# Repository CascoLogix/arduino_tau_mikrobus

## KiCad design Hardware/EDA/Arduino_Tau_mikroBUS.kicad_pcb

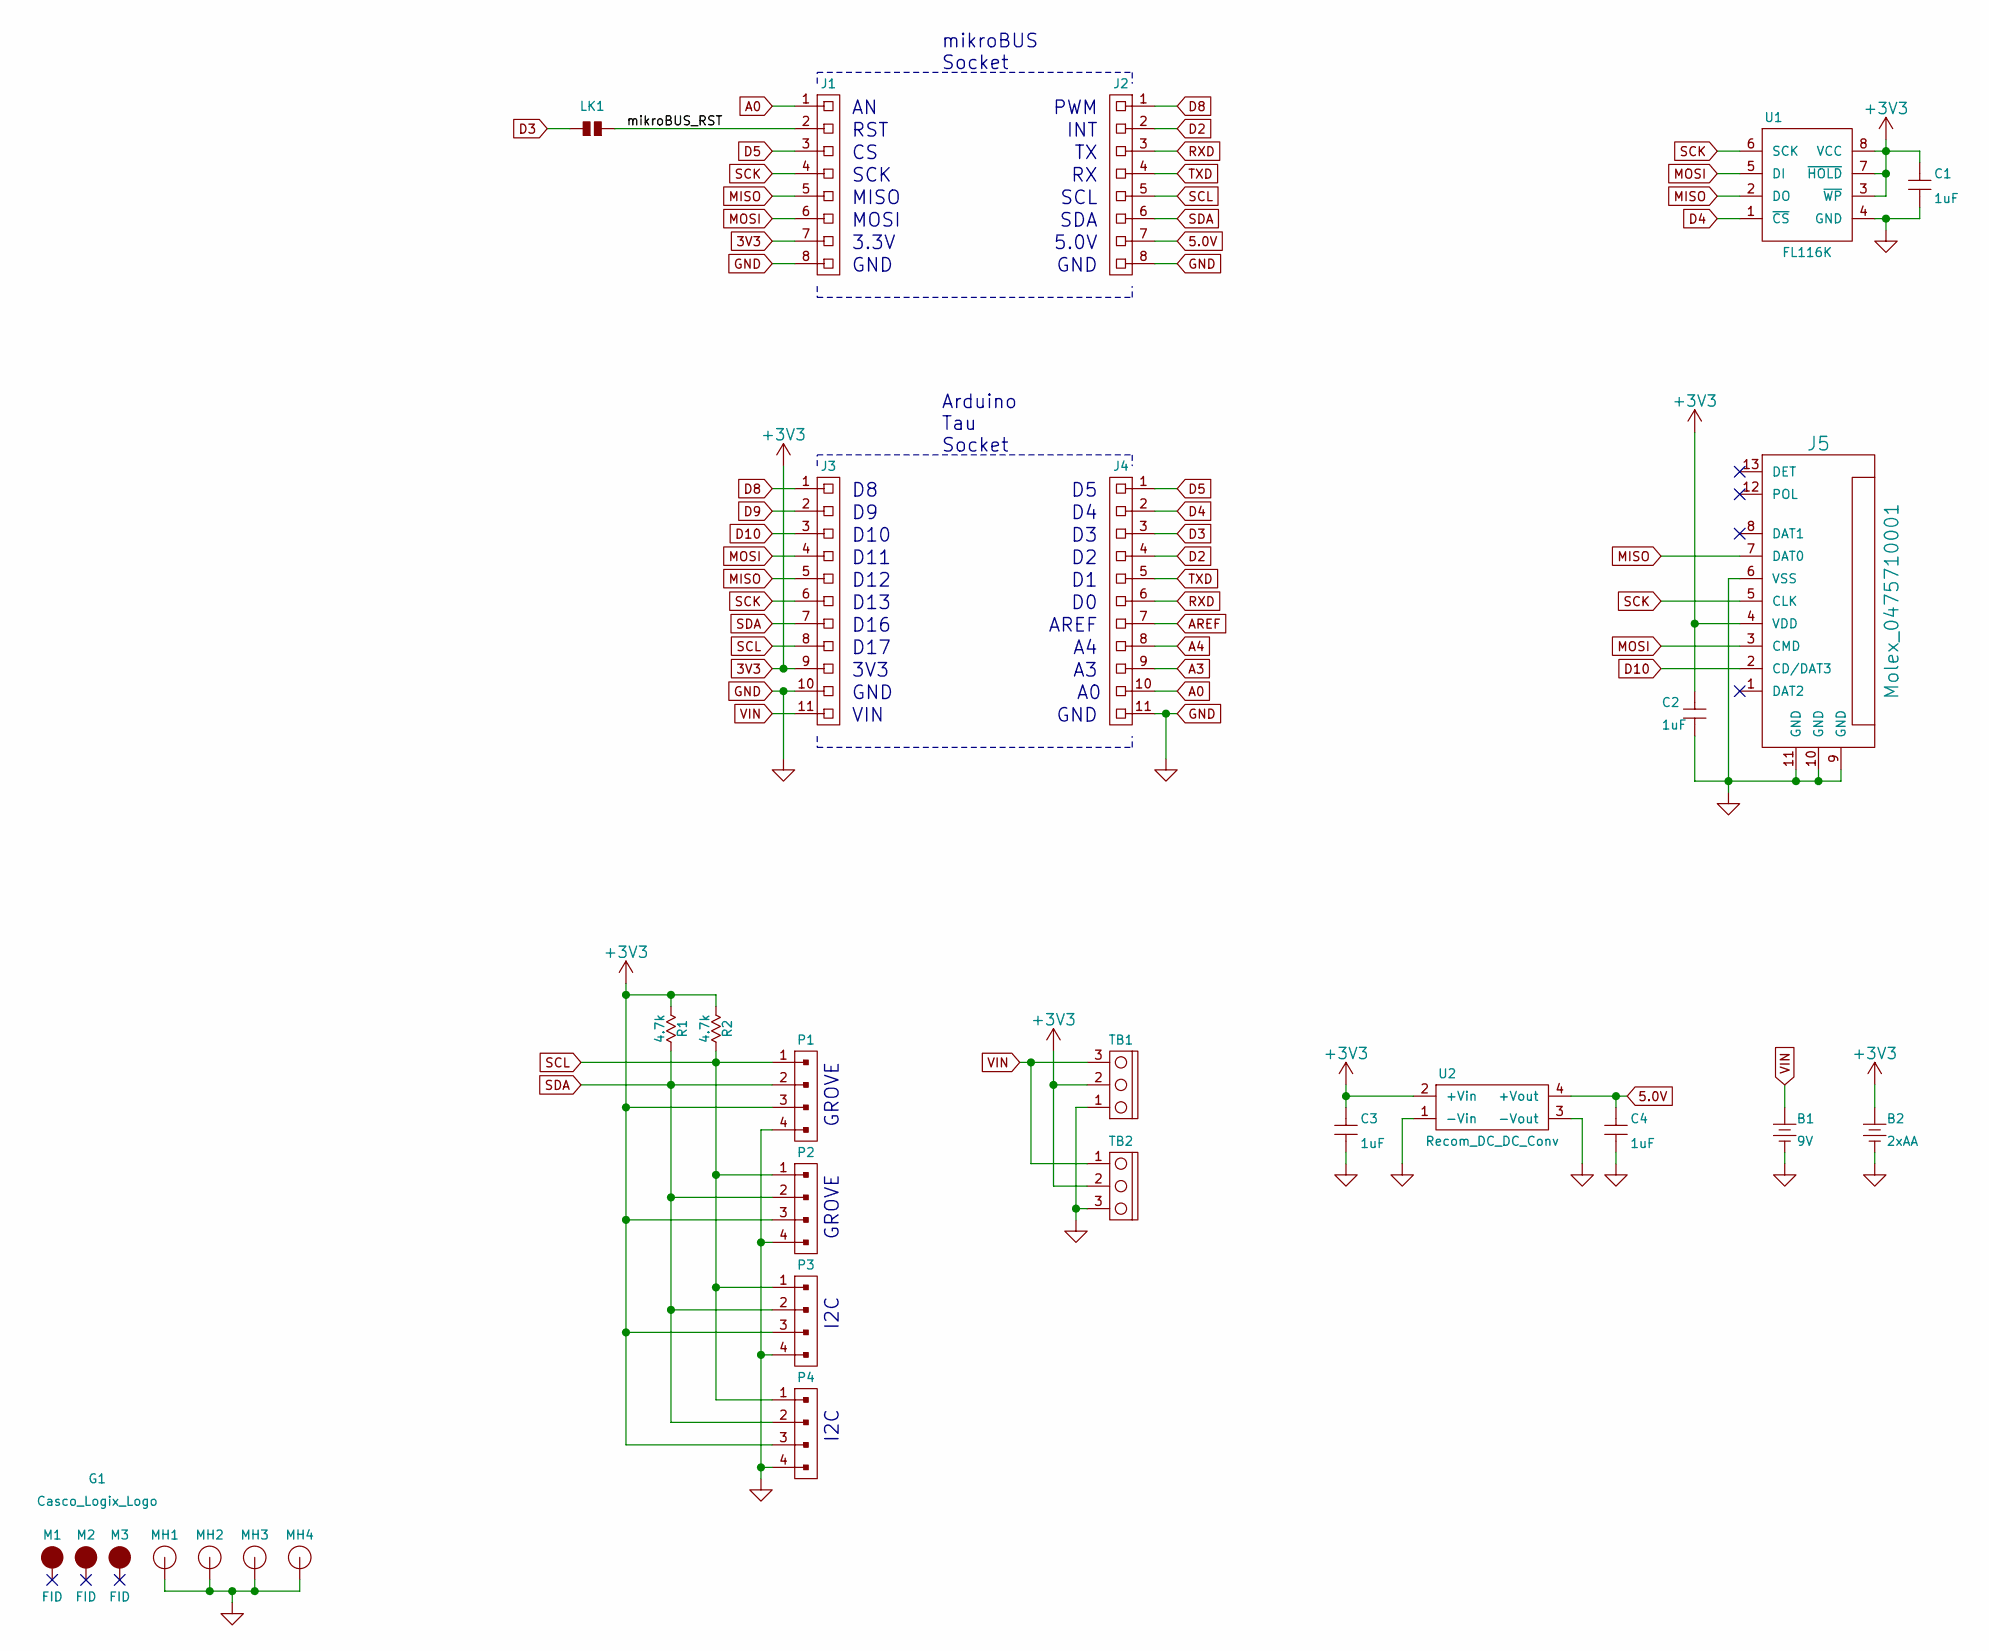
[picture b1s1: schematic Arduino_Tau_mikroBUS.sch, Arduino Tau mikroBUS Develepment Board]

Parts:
B1: 9V; BC9VPC
B2: 2xAA; Keystone_2462_2AA
C1, C2, C3, C4: 1uF; 0603
G1: Casco_Logix_Logo; Casco_Logix_Logo_7x7MM
J1, J2: HEADER_F_2.54MM_1R8P_ST_AU_PTH
J3, J4: HEADER_F_2.54MM_1R11P_ST_AU_PTH
J5: Molex_0475710001
LK1: SOLDER_LINK_NO
M1, M2, M3: FID; FIDUCIAL
MH1, MH2, MH3, MH4: MTG_HOLE; MH_#6
P1, P2, P3, P4: HEADER_M_2.54MM_1R4P_ST_AU_PTH
R1, R2: 4.7k; R0603
TB1, TB2: OSTVN_1x3; TB_100MIL_1R3P_PTH
U1: FL116K; SO-8
U2: Recom_DC_DC_Conv; Recom_ROE-3.305S

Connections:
3V3: B2.1 (+), C1.1, C2.1, C3.1, J1.7, J3.9, J5.4 (VDD), P1.3, P2.3, P3.3, P4.3, R1.1, R2.1, TB1.2, TB2.2, U1.3 (~WP), U1.7 (~HOLD), U1.8 (VCC), U2.2 (+Vin)
5.0V: C4.1, J2.7, U2.4 (+Vout)
/mikroBUS_RST: J1.2, LK1.2
A0: J1.1, J4.10
A3: J4.9
A4: J4.8
AREF: J4.7
D2: J2.2, J4.4
D3: J4.3, LK1.1
D4: J4.2, U1.1 (~CS)
D5: J1.3, J4.1
D8: J2.1, J3.1
D9: J3.2
D10: J3.3, J5.2 (CD/DAT3)
GND: B1.2 (-), B2.2 (-), C1.2, C2.2, C3.2, C4.2, J1.8, J2.8, J3.10, J4.11, J5.6 (VSS), J5.9 (GND), J5.10 (GND), J5.11 (GND), MH1.~, MH2.~, MH3.~, MH4.~, P1.4, P2.4, P3.4, P4.4, TB1.1, TB2.3, U1.4 (GND), U2.1 (-Vin), U2.3 (-Vout)
MISO: J1.5, J3.5, J5.7 (DAT0), U1.2 (DO)
MOSI: J1.6, J3.4, J5.3 (CMD), U1.5 (DI)
RXD: J2.3, J4.6
SCK: J1.4, J3.6, J5.5 (CLK), U1.6 (SCK)
SCL: J2.5, J3.8, P1.1, P2.1, P3.1, P4.1, R2.2
SDA: J2.6, J3.7, P1.2, P2.2, P3.2, P4.2, R1.2
TXD: J2.4, J4.5
VIN: B1.1 (+), J3.11, TB1.3, TB2.1

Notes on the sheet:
mikroBUS Socket
Arduino Tau Socket
RST
SCK
MISO
MOSI
3.3V
GND
PWM
INT
SCL
SDA
5.0V
D10
3V3
VIN
AREF
GROVE
I2C
D11
D12
D13
D16
D17

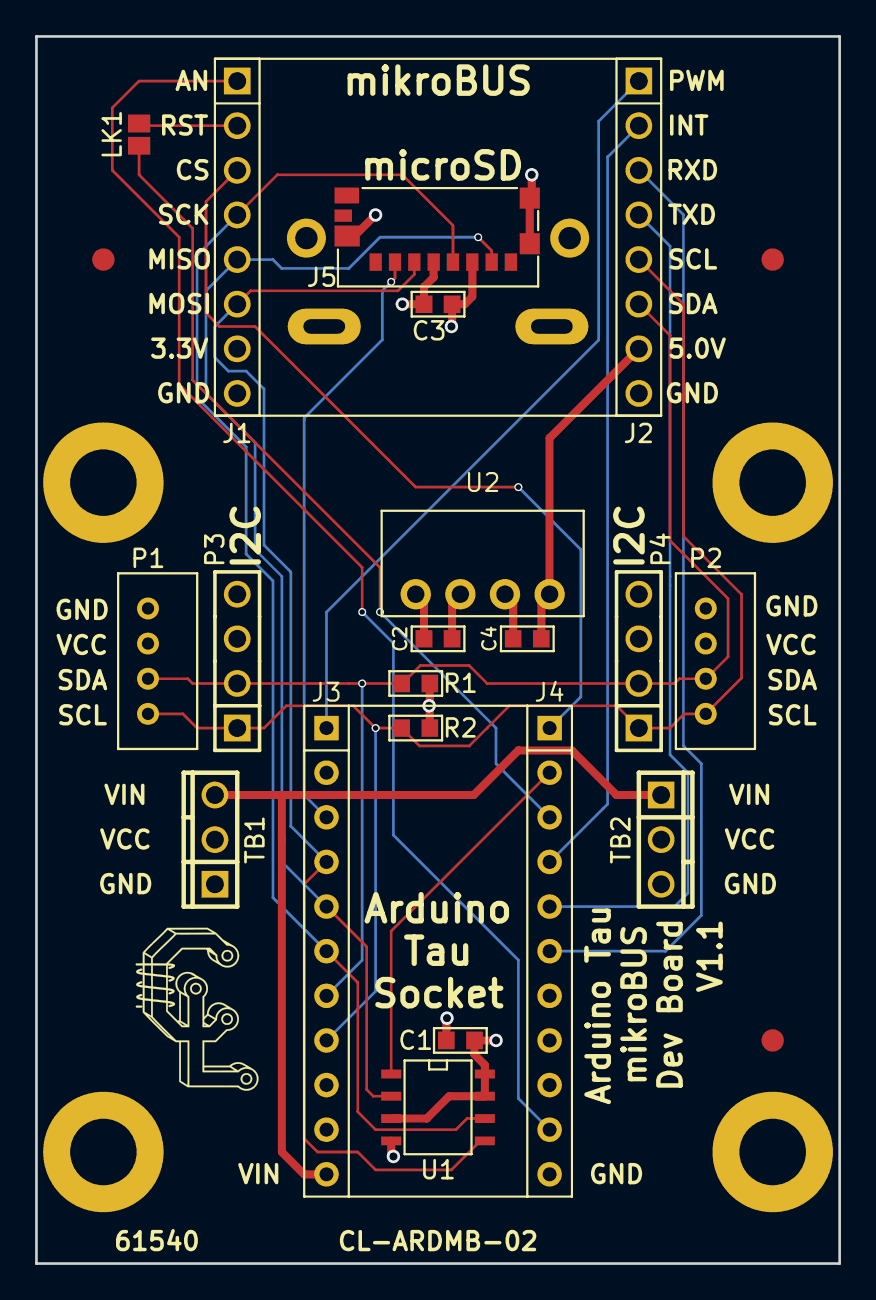
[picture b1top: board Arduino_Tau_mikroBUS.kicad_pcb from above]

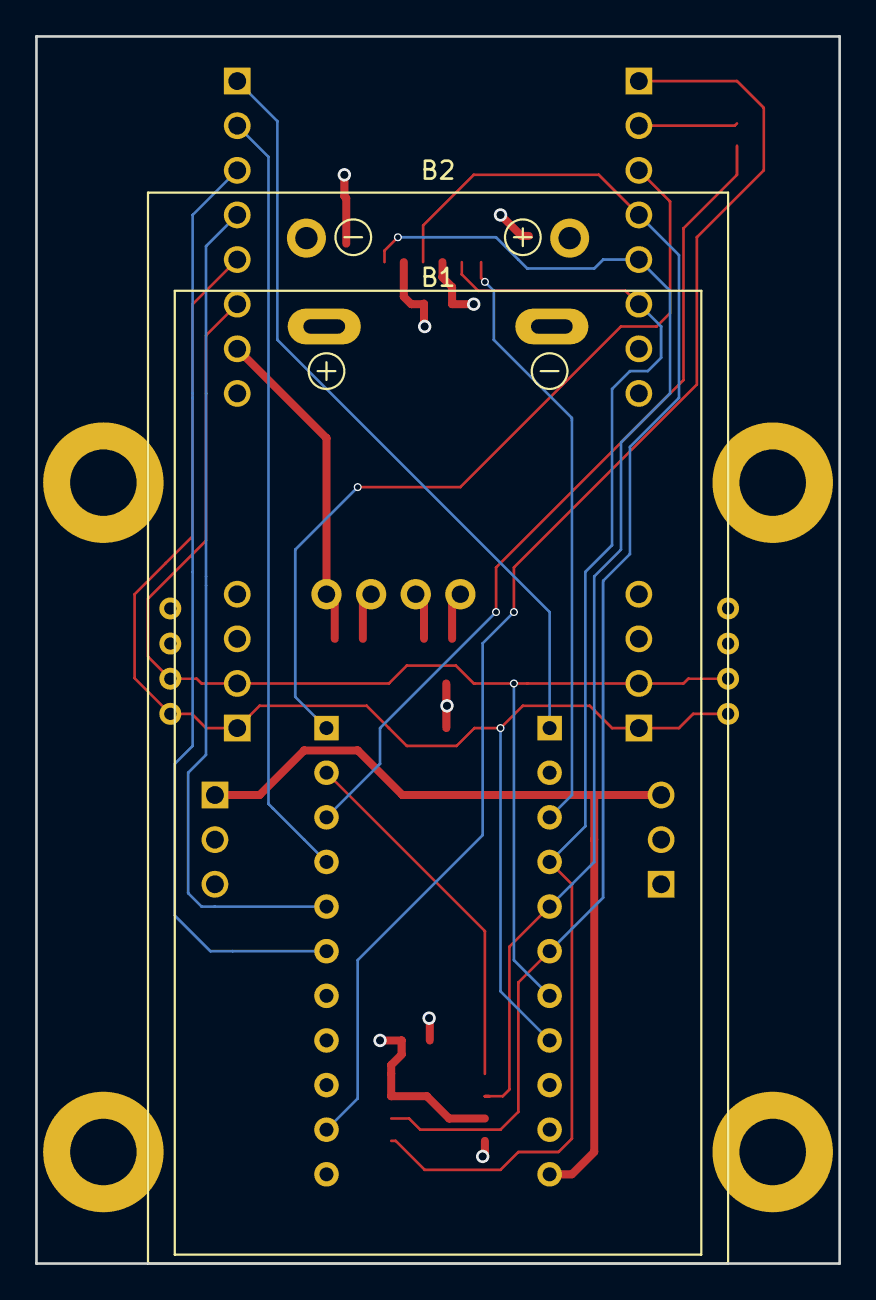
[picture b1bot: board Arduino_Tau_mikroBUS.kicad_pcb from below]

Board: 4 copper layers, 45.7 x 69.8 mm, 30 parts (2 on the bottom side), 19 nets.

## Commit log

2017-12-28 Initial commit.
2017-12-28 Updated schematic and gerbers. Added silkscreen artwork and 3D component models.
2017-12-28 Updated silkscreen artwork and regenerated gerbers.
2017-12-28 Corrected part# on silkscreen artwork.
2017-12-29 Added PCB render image.
2018-01-06 Changed PCB outline/size to accomodate mounting holes, but still fit in enclosure. Regenerated Gerbers and PCB render images.
2018-02-17 Finished updates.
2018-02-17 Final changes prior to gerber verification.
2018-02-24 Added sample sketches
2018-02-25 Split code into functional files. Menu listed order was changed and is now out of sync with menu function execution. Verified menu still displays on startup.
2018-02-25 Added remaining missing function outlines, code compiles.
2018-02-25 Finished coding serial configuration menu and related functions to save/load to/from flash chip. Added framework files to start on functionality to load configuration from uSD card.
2018-02-25 Fixed bug preventing menu exit.
2018-02-26 Updated to start including new boot functionality regarding serial interface, serial interface timeout, and SD card interface. Compiles, but not much testing yet.
2018-04-07 Moved two traces near MH2. Verified gerbers.
